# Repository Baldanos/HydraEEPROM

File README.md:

# HydraEEPROM - Hydrabus EEPROM shield

This shield is made to simplify operations on small I2C and SPI EEPROMS in SOIC8
format. It is better combined with a SOIC8 clip like [these
ones](https://www.aliexpress.com/wholesale?SearchText=soic8+clip).

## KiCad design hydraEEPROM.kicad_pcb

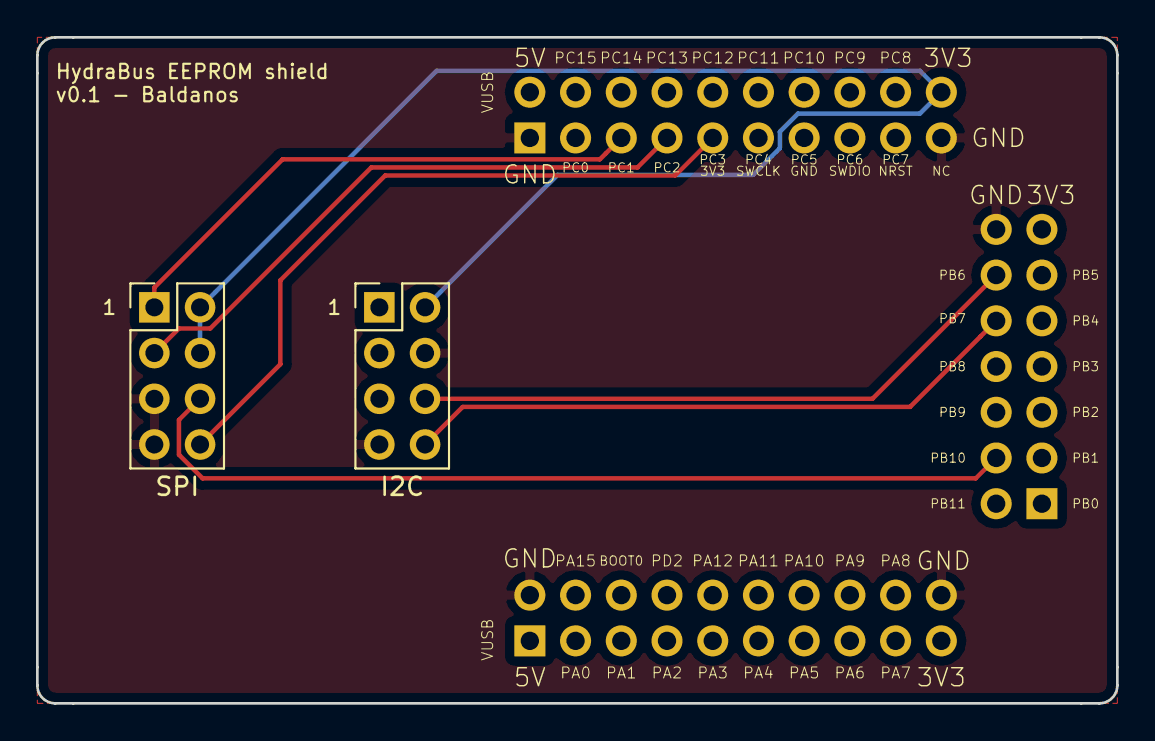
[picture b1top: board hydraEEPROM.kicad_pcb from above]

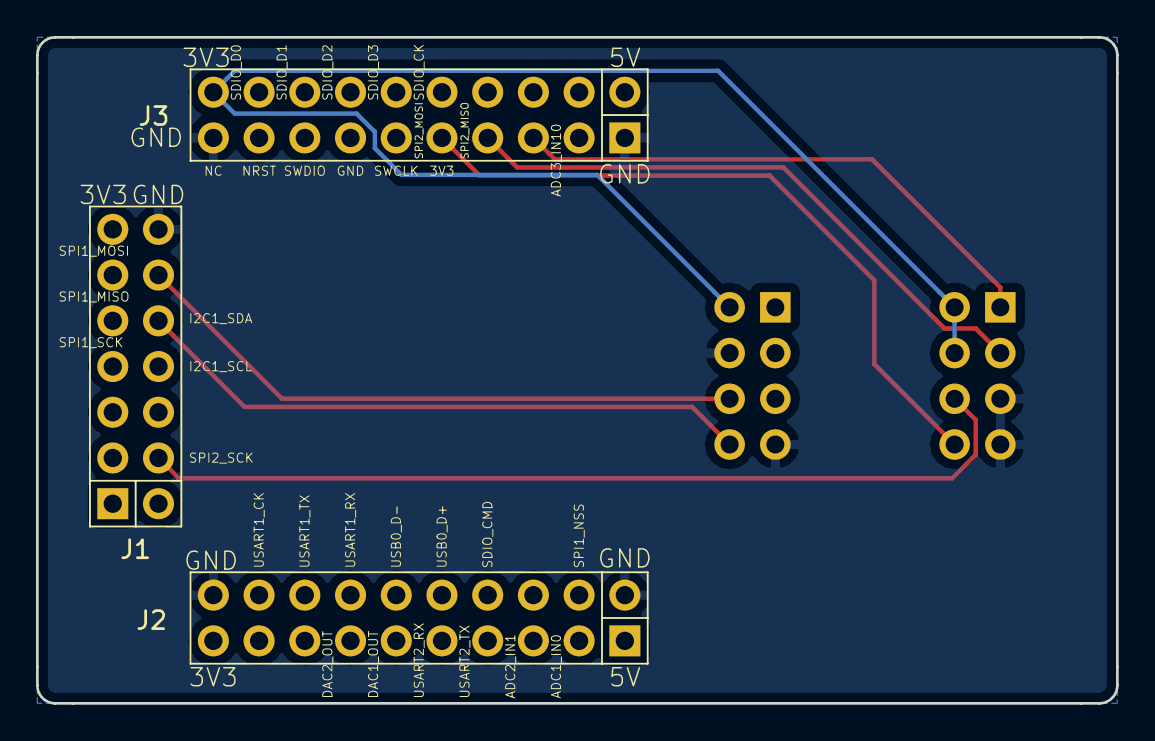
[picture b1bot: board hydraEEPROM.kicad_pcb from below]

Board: 2 copper layers, 60.0 x 37.0 mm, 5 parts (3 on the bottom side), 9 nets.

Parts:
J1: CONN_02X07; Hydrabus_Shield_Conn_2x07
J2, J3: CONN_02X10; Hydrabus_Shield_Conn_2x10
J5: SPI; Pin_Header_Straight_2x04_Pitch2.54mm
J6: I2C; Pin_Header_Straight_2x04_Pitch2.54mm

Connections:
+3V3: J1.13, J2.19, J3.20, J5.2, J5.4, J6.2
+5V: J2.1, J3.2
GND: J1.14, J2.2, J2.20, J3.1, J3.19, J5.5, J5.7, J6.4, J6.7
i2c_scl: J1.12, J6.6
i2c_sda: J1.10, J6.8
spi_cs: J3.5, J5.1
spi_miso: J3.7, J5.3
spi_mosi: J3.9, J5.8
spi_sck: J1.4, J5.6

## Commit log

2018-12-26 Initial release

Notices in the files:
hydraEEPROM.kicad_pcb:
CC BY-SA 4.0
